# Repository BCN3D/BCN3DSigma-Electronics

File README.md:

# BCN3D Electronics

This repository will hold all the information about the Electronics of the BCN3D Sigma.

As a declared Open Source organization, it's in our mission to release all the original design files to you to be able to learn, reuse and improve. Open Source not only means code, it also concerns hardware.

We've managed to design and manufacture our custom Electronics for the BCN3D Sigma in many ways thanks to the community and other Open Source Hardware projects.
BCN3D Electronics is a mashup between the [Ultimaker 2 Board](https://github.com/Ultimaker/Ultimaker2) , the [Megatronics v3.0](http://reprap.org/wiki/Megatronics_3.0) and some others...

## Design concept

The BCN3D Electronics is intended to be modular and custom fitted in our BCN3D Sigma 3D printer and that's why we made some design decisions.

1. Stepper drivers out of the Mainboard. As the drivers generate quite a lot of heat, we've moved them nearest as possible to the corresponding stepper motor. If one fails, you just have to replace a cheap stepper driver board. This way, we've managed to fit an entire electronics system without a fan.
2. FFC's everywhere. The BCN3D Sigma is an Independent Dual Extruder Printer so the Electronics supports 6  Axis of movement. Thats a lot of wires and wires takes some precious space. We decided to go with a Flat Flexible Cable solution that keeps things organized and it's faster to assemble.
3. 24VDC Power Supply. The performance improves as the whole Electronics run cooler while maintaining a very low voltage system.  
4. Full Color Resistive Touch Screen. The electronics is compatible with 4D Systems Displays out of the box. We think the user should interact with an intuitive interface to be able to use the printer easily even without previous experience in 3D printing.

## Boards

+ **Mainboard:** This board holds the microcontroller, the 5V switching power supply, the power outputs and the thermistor inputs. It has a USB interface for upgrading the firmware and communicating with the printer via serial port.
+ **Stepper Driver:** We carry the well-known DRV8825 stepper driver from Texas Instruments. It's able to supply plenty of power for all the types of stepper motors in the BCN3D Sigma.
+ **Extruder Board:** It's a simple interconnection board between the Mainboard and the components of the hotend assembly. With just one Flat Flexible Cable you the microcontroller has control over the hotend, the thermistor and endstop readings and the layer fan.
+ **Heated Bed:** As the platform size of the BCN3D Sigma is quite big, we've made a custom A4 size heated bed to achieve the performance required. It can heat up to 100ºC in about 6-8 minutes and keep that temperature for long period of times.
+ **SD Reader:** We've design our own SD Reader module with better signal integrity and better power supply requirements. This board has been designed entirely in [KiCAD Open Source software](http://kicad.org/). 

## Production

We strongly believe that using high quality components has an effect on the electronics performance as well as in the printer performance.

This is why we ensure components quality and control of the production process by designing and manufacturing in Barcelona. In this manner we iterate faster, reducing time to market.

Being in control of all the supply chain allows us to optimize designs and reduce costs.

## Contributing

If you own a BCN3D Sigma and electronics is your thing, feel free to post an [issue](https://github.com/BCN3D/BCN3D-Electronics/issues). We know this is still an 8-bit platform but we're working on optimizing it to the max and thinking in the next generation of 3D Printing Electronics. Always Open Source.

### License

Under the **LICENSE** folder you'll find all the information about the license. We've chosen CERN Open Hardware License and you must follow the guidelines as we had. All the documentation is available to you to study it, modify it and share it.
In addition, if modifications are made and distributed, it must be under the same licence conditions – this is the ‘persistent’ nature of the licence, which ensures that the whole community will continue benefiting from improvements, in the sense that everyone will in turn be able to make modifications to these improvements.

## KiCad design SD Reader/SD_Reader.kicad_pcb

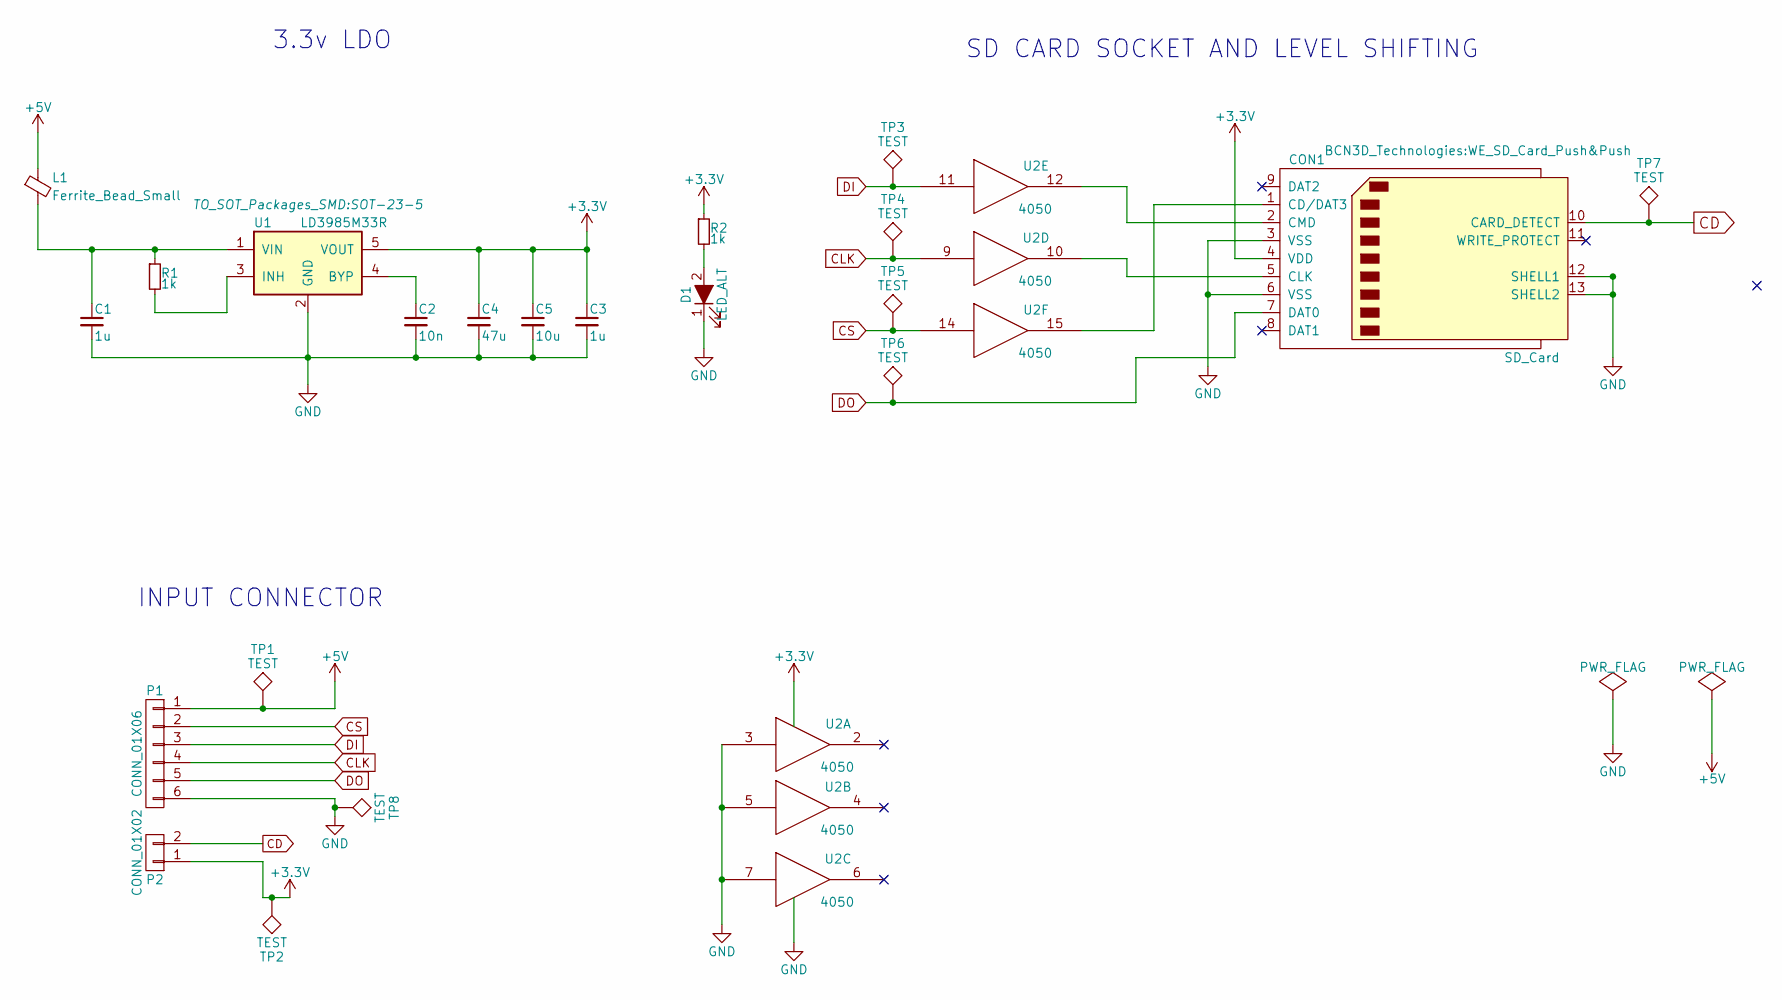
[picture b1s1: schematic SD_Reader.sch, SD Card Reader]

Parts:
C1, C3: 1u; C_0603
C2: 10n; C_0603
C4: 47u; C_1210
C5: 10u; C_0805
CON1: SD_Card; WE_SD_Card_Push&Push
D1: LED_ALT; LED_0603
L1: Ferrite_Bead_Small; R_0603
P1: CONN_01X06; Pin_Header_Straight_1x06_Pitch2.54mm_SMD_Pin1Right
P2: CONN_01X02; Pin_Header_Straight_1x02_Pitch2.54mm
R1, R2: 1k; R_0603
TP1, TP2, TP3, TP4, TP5, TP6, TP7, TP8: TEST; Measurement_Point_Round-SMD-Pad_Small
U1: LD3985M33R; SOT-23-5
U2: 4050; SO-16-N

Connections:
+3V3: C3.1, C4.1, C5.1, CON1.4 (VDD), P2.1, R2.1, TP2.1, U1.5 (VOUT), U2.1 (VCC)
+5V: L1.1, P1.1, TP1.1
CD: CON1.10 (CARD_DETECT), P2.2, TP7.1
CLK: P1.4, TP4.1, U2.9
CS: P1.2, TP5.1, U2.14
DI: P1.3, TP3.1, U2.11
DO: CON1.7 (DAT0), P1.5, TP6.1
GND: C1.2, C2.2, C3.2, C4.2, C5.2, CON1.3 (VSS), CON1.6 (VSS), CON1.12 (SHELL1), CON1.13 (SHELL2), D1.1 (K), P1.6, TP8.1, U1.2 (GND), U2.3, U2.5, U2.7, U2.8 (VSS)
unnamed: C1.1, L1.2, R1.1, U1.1 (VIN)
unnamed: C2.1, U1.4 (BYP)
unnamed: CON1.1 (CD/DAT3), U2.15
unnamed: CON1.2 (CMD), U2.12
unnamed: CON1.5 (CLK), U2.10
unnamed: D1.2 (A), R2.2
unnamed: R1.2, U1.3 (INH)

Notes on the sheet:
INPUT CONNECTOR
SD CARD SOCKET AND LEVEL SHIFTING
3.3v LDO

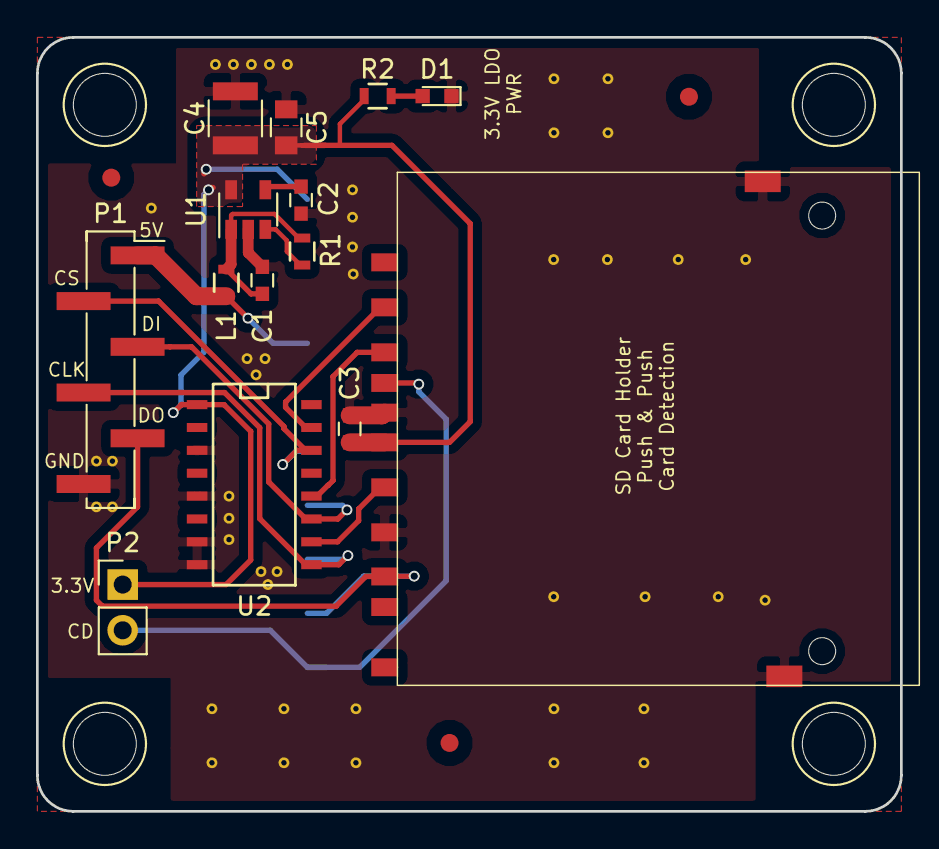
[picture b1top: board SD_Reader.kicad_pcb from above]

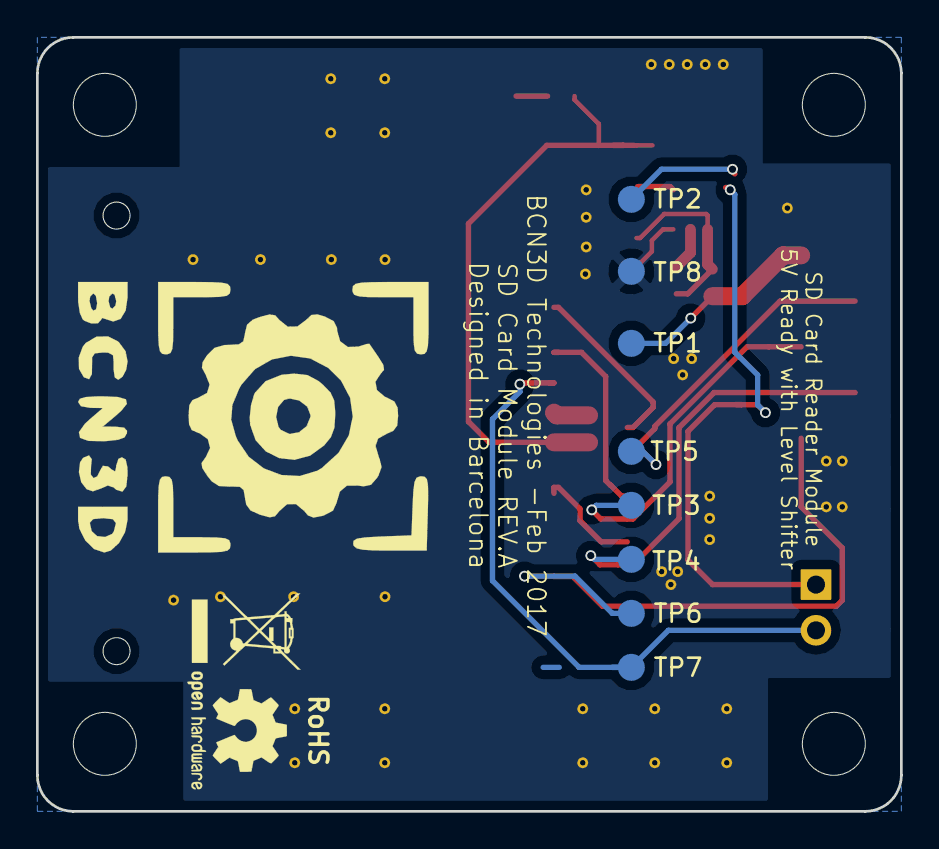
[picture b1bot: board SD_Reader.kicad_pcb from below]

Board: 2 copper layers, 48.0 x 43.0 mm, 22 parts (8 on the bottom side), 15 nets.

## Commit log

2014-11-21 Adding the first files to git.This is the revision A of the boards
2014-11-21 Main Board almost ready
    5V rail to ICSP and some headers left to connect
2014-11-25 New File Tree and Updates
2014-11-27 Just git ignore and gitattributes
2014-12-24 Updates!
    Rev_A Ready and firsts prototypes
2014-12-29 Updated files
2015-02-13 The new REV_B has been shipped to production
    New MainBoard Design, new Stepper drivers and new Extruder Board.
    We also added many new components and configurations
2016-04-08 BCN3D Electronics REV.E tested and manufactured
2016-04-29 Updated README
    new sections
2016-04-29 gitignore
2016-05-04 CERN OHL Added!
    Also updated the README doc
2016-05-04 typos
2016-05-11 Fixed thermistor series resistors
    Added new license info and WEEE/FCC/CE Logo.
2016-09-27 Extruder board REV. F now on production
    New Extruder Board design for the late 2016 BCN3D Sigma 3D Printer
2016-09-27 Silent Stepper Driver TMC2130 based REV.B
    2 Layer board for the TMC2130 based Stepper Driver board
2016-10-24 Update Ignore File and delete Eagle Lock files
2016-10-28 Added img folder for the wiki
2016-11-02 Add GIFS for the wiki
2016-11-02 Motherboard updated to new version REV.G
    Basically the only change in REV.G is the 20 contacts Flat Flexible
    Cable connector.
2017-02-09 File for the REV.H
    Files from the REV.H Released with new and more documentation.
2017-02-09 Added GERBER Files
2017-03-09 Added Gitter badge link
2017-04-11 New SD Reader
    Add first revision files REVA
2017-04-11 update README for the SD Reader
2018-01-18 License upgrade
2021-11-09 Update README.md
    https://forum.kicad.info/t/warning-avoid-all-links-to-kicad-pcb-org-use-kicad-org/31521
